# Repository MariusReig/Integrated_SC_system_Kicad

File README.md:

# Integrated_SC_system_Kicad
This repository contains the schematics and layout for an integrated supercapacitor system design.

Some changes is done in the schematic after the prototype was constructed. This includes:
- Removed schotky diode and auto-balancing in the cell balancing circuitry. 
- Adjusted cell-balancing resistance. 
- Adjusted pull-up resistor in the OVP. This is also done to the prototype.
- Charge and pre-charge gate-signal on isolated end is switched. 

Notes from testing of the prototype:
- The prototype is able to charge without any gatesignal through the pre-charge mosfet. Gatesignal is required to utilize charge and load. 
- The auto-balancing IC does not work as intended. Seems to be working for one cell of the two connected for each. Go back and check connections or use only resistor balancing. 
The design with balancing two-and-two cells is not great and needs work. Also caused the voltage potential over some odd-number cells to become negative. The voltage potential over the two first cells affected another, causing the even cell to receive more charge. A quick fix was to remove the IC and solder on 160ohm balancing resistance for each cell. The prototype was then balanced properly and tests was carried out. 
- The schotky diode was removed to test if it was a potential error-source. It was not. 
- The OVP circuit did not work. Since all 12 circuits are connected to the same 5V_ISO supply all will be pulled to ground unless all are active at the same time. The differential amplifier works as intended, but not the votlage detection IC. Tests on the IC can be carried out to check if it works as designed.

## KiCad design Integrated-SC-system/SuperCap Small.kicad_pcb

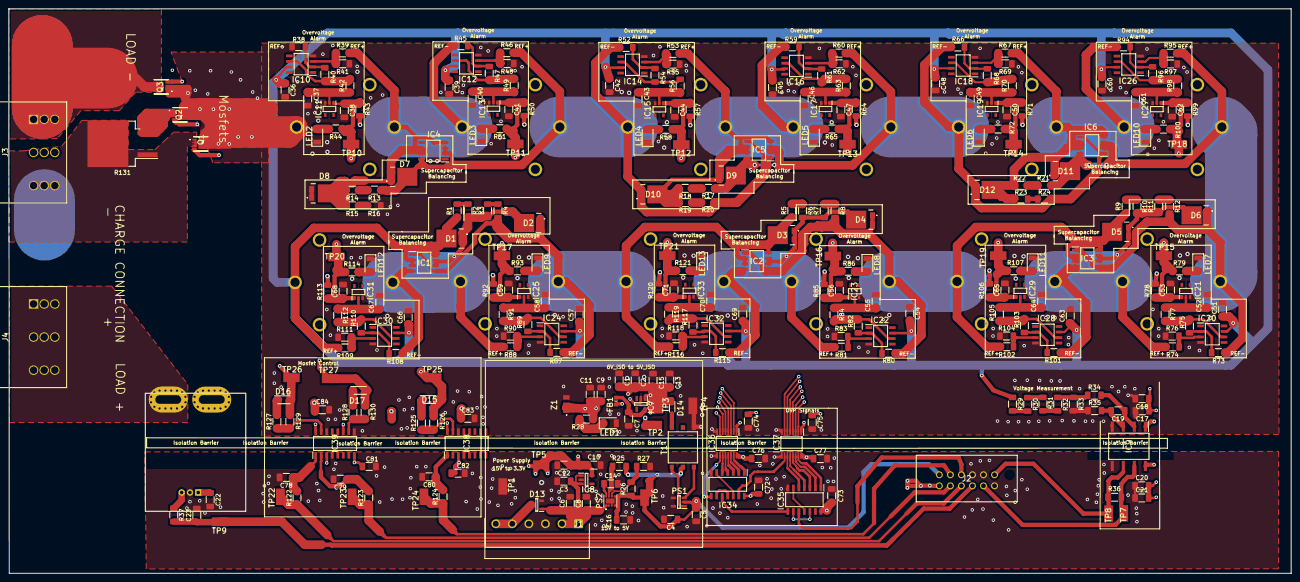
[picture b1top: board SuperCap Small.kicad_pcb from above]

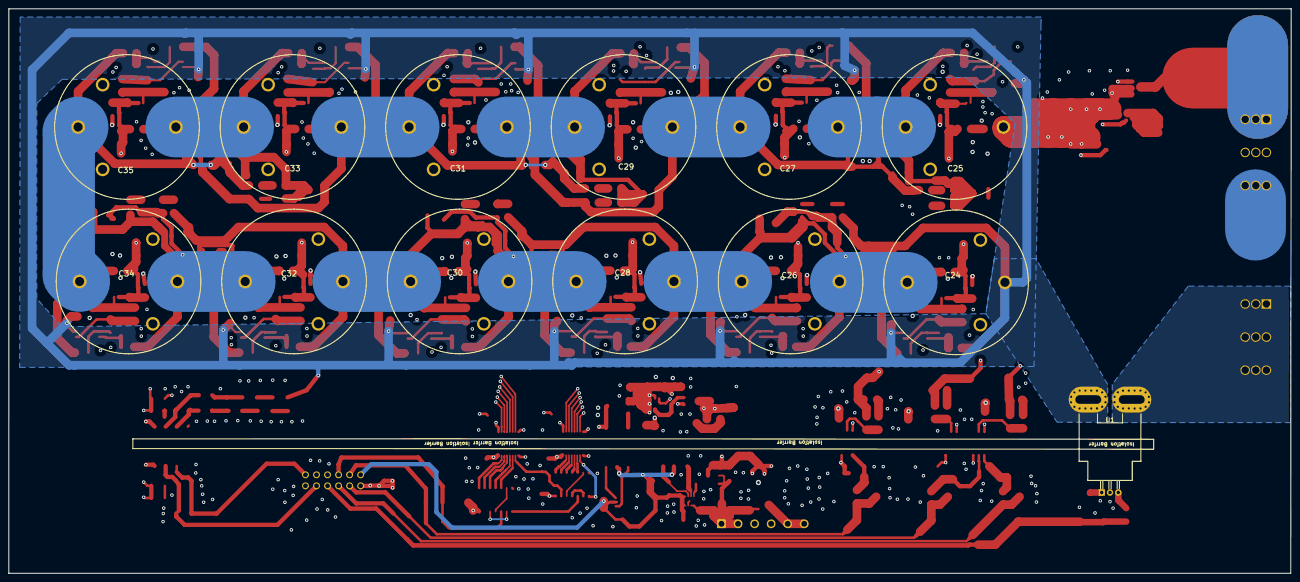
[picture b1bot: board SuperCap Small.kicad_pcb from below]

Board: 4 copper layers, 295.2 x 129.9 mm, 324 parts (13 on the bottom side), 159 nets.

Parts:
C1, C4, C7, C9, C13: 0.01u; C_1206_3216Metric_Pad1.33x1.80mm_HandSolder
C2, C5, C11, C12, C15: 100p; C_1206_3216Metric_Pad1.33x1.80mm_HandSolder
C3, C18, C21, C23, C83, C84: 1u; C_1206_3216Metric_Pad1.33x1.80mm_HandSolder
C6: 470p; C_1206_3216Metric_Pad1.33x1.80mm_HandSolder
C8: 10u; C_1206_3216Metric_Pad1.33x1.80mm_HandSolder
C10: 2.2u; C_1206_3216Metric_Pad1.33x1.80mm_HandSolder
C14: 430p; C_1206_3216Metric_Pad1.33x1.80mm_HandSolder
C16: 22u; C_1206_3216Metric_Pad1.33x1.80mm_HandSolder
C17, C20, C22, C36, C37, C38, C39, C40, C41, C42, C43, C44, C45, C46, C47, C48, C49, C50, C51, C52, C53, C54, C55, C56, C57, C58, C59, C60, C61, C62, C63, C64, C65, C66, C67, C68, C69, C70, C71, C72, C73, C74, C75, C76, C77, C78, C79, C80, C81, C82: 0.1u; C_1206_3216Metric_Pad1.33x1.80mm_HandSolder
C19: 330p; C_1206_3216Metric_Pad1.33x1.80mm_HandSolder
C24, C25, C26, C27, C28, C29, C30, C31, C32, C33, C34, C35: BCAP0360_P270_S18; BCAP0350P270S18
D1, D2, D3, D4, D5, D6, D7, D8, D9, D10, D11, D12: FSV10100V; FSV20100V
D13: PESD15VL2BT,215; SOT95P230X110-3N
D14: PMEG2005EJ,115; SODFL2512X80N
D15, D16, D17: RS07D-HM3-08; SODFL3718X108N
FB1: MMZ1608B102CTA00; BEADC1608X95N
IC1, IC2, IC3, IC4, IC5, IC6: ALD910017SALI; SOIC127P600X175-8N
IC7: LD2985BM50R; SOT95P280X145-5N
IC8: MIC5225-3.3YM5-TR; SOT95P280X145-5N
IC9: AMC1100DUBR; SOP254P1040X485-8N
IC10, IC12, IC14, IC16, IC18, IC20, IC22, IC24, IC26, IC28, IC30, IC32: OPA197IDR; SOIC127P600X175-8N
IC11, IC13, IC15, IC17, IC19, IC21, IC23, IC25, IC27, IC29, IC31, IC33: BD4827G-TR; SOT95P280X125-5N
IC34, IC35: SN74HCS4075QDRQ1; SOIC127P600X175-14N
IC36, IC37: ISO7760FQDBQQ1; SOP64P600X175-16N
IC38, IC39: UCC21220AD; SOIC127P600X175-16N
J1: 691322310006; SHDRRA6W80P0X381_1X6_2405X920X700P
J2: 15-47-7512; 15477512
J3, J4: 1717017
LED1, LED2, LED3, LED4, LED5, LED6, LED7, LED8, LED9, LED10, LED11, LED12, LED13: APTD3216LSYCK; LEDC3216X200N
PS1: SN6501DBVR; SOT95P280X145-5N
PS2: TPS82130SILT
Q1, Q2, Q3: BSZ024N04LS6ATMA1
R1, R2, R3, R4, R5, R6, R7, R8, R9, R10, R11, R12, R13, R14, R15, R16, R17, R18, R19, R20, R21, R22, R23, R24, R44, R51, R58, R65, R72, R79, R86, R93, R100, R107, R114, R121: 400; R_1206_3216Metric_Pad1.30x1.75mm_HandSolder
R25, R27: 100k; R_1206_3216Metric_Pad1.30x1.75mm_HandSolder
R26: 523k; R_1206_3216Metric_Pad1.30x1.75mm_HandSolder
R28: 3.16; R_1206_3216Metric_Pad1.30x1.75mm_HandSolder
R29, R30, R31, R32: 59.7; R_1206_3216Metric_Pad1.30x1.75mm_HandSolder
R33, R43, R50, R57, R64, R71, R78, R85, R92, R99, R106, R113, R120: 1k; R_1206_3216Metric_Pad1.30x1.75mm_HandSolder
R34, R35: 12; R_1206_3216Metric_Pad1.30x1.75mm_HandSolder
R36, R37, R125, R126, R127, R128, R129, R130: R; R_1206_3216Metric_Pad1.30x1.75mm_HandSolder
R38, R39, R40, R41, R42, R45, R46, R47, R48, R49, R52, R53, R54, R55, R56, R59, R60, R61, R62, R63, R66, R67, R68, R69, R70, R73, R74, R75, R76, R77, R80, R81, R82, R83, R84, R87, R88, R89, R90, R91, R94, R95, R96, R97, R98, R101, R102, R103, R104, R105, R108, R109, R110, R111, R112, R115, R116, R117, R118, R119: 10k; R_1206_3216Metric_Pad1.30x1.75mm_HandSolder
R122, R123, R124: rc; R_1206_3216Metric_Pad1.30x1.75mm_HandSolder
R131: 30; TO-263-2_TabPin1
T1: 760390015
TP1, TP2, TP3, TP4, TP5, TP6, TP7, TP8, TP9, TP10, TP11, TP12, TP13, TP14, TP15, TP16, TP17, TP18, TP19, TP20, TP21, TP22, TP23, TP24, TP25, TP26, TP27: 5019
U1: ACS758LCB-050B-PFF-T; Allegro_CB_PFF
Z1: DFLZ6V2-7; DFLZ6V87

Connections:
3.3V: C10.1, C12.1, C20.2, C21.2, C22.1, C72.1, C73.1, C76.1, C77.1, C81.1, C82.1, IC8.5, IC9.8, IC34.14, IC35.14, IC36.16, IC37.16, IC38.3, IC39.3, IC39.8, J2.B6, TP5.1, U1.1
5V: C4.1, C5.1, C16.1, J2.A6, PS1.2, PS2.4, PS2.5, R25.1, R26.1, T1.2, TP6.1
5V_ISO: C9.2, C11.2, C17.1, C18.1, C74.1, C75.1, FB1.1, IC9.1, IC36.1, IC37.1, R28.1, R43.2, R50.2, R57.2, R64.2, R71.2, R78.2, R85.2, R92.2, R99.2, R106.2, R113.2, R120.2, TP2.1, Z1.1
6V_ISO: C1.2, C2.2, C13.2, C15.1, C83.1, C84.1, D14.1, IC7.1, IC38.16, IC39.11, IC39.16, TP3.1
15V_global: C3.1, C6.1, C8.1, D13.1, IC8.1, IC8.3, J1.1, J1.2, PS2.1, PS2.2
/Isolation-IC/IN_PORT_1: C68.1, IC31.1, IC36.7, R113.1, R114.1, TP20.1
/Isolation-IC/IN_PORT_2: C59.1, IC25.1, IC36.5, R92.1, R93.1, TP17.1
/Isolation-IC/IN_PORT_3: C71.1, IC33.1, IC36.2, R120.1, R121.1, TP21.1
/Isolation-IC/IN_PORT_4: C56.1, IC23.1, IC37.7, R85.1, R86.1, TP16.1
/Isolation-IC/IN_PORT_5: C65.1, IC29.1, IC37.4, R106.1, R107.1, TP19.1
/Isolation-IC/IN_PORT_6: C53.1, IC21.1, IC37.2, R78.1, R79.1, TP15.1
/Isolation-IC/IN_PORT_7: C62.1, IC27.1, IC37.3, R99.1, R100.1, TP18.1
/Isolation-IC/IN_PORT_8: C50.1, IC19.1, IC37.5, R71.1, R72.1, TP14.1
/Isolation-IC/IN_PORT_9: C47.1, IC17.1, IC37.6, R64.1, R65.1, TP13.1
/Isolation-IC/IN_PORT_10: C44.1, IC15.1, IC36.3, R57.1, R58.1, TP12.1
/Isolation-IC/IN_PORT_11: C41.1, IC13.1, IC36.4, R50.1, R51.1, TP11.1
/Isolation-IC/IN_PORT_12: C38.1, IC11.1, IC36.6, R43.1, R44.1, TP10.1
/OR-GATE/IN_PORT_1: IC34.8, IC36.10
/OR-GATE/IN_PORT_2: IC34.4, IC36.12
/OR-GATE/IN_PORT_3: IC34.1, IC36.15
/OR-GATE/IN_PORT_4: IC34.13, IC37.10
/OR-GATE/IN_PORT_5: IC35.3, IC37.13
/OR-GATE/IN_PORT_6: IC35.1, IC37.15
/OR-GATE/IN_PORT_7: IC35.4, IC37.12
/OR-GATE/IN_PORT_8: IC35.2, IC37.14
/OR-GATE/IN_PORT_9: IC35.5, IC37.11
/OR-GATE/IN_PORT_10: IC34.2, IC36.14
/OR-GATE/IN_PORT_11: IC34.3, IC36.13
/OR-GATE/IN_PORT_12: IC34.5, IC36.11
/Precharge/CHARGE_INN: J3.7, J3.8, J3.9, Q1.1, Q1.2, Q1.3, Q1.9, R131.1
/Precharge/Charge_Active: J2.B5, R123.1, TP23.1
/Precharge/LOAD_INN: J3.1, J3.2, J3.3, Q3.5, Q3.6, Q3.7, Q3.8, Q3.10
/Sheet6014032E/Current_TBM+: J4.1, J4.2, J4.3, J4.4, J4.5, J4.6, J4.7, J4.8, J4.9, U1.4
/Signaling/ADCINA0_AI: C23.1, J2.B3, R37.2, TP9.1
/Signaling/ADCINA2_AI: IC9.7, J2.B2, R36.1, TP7.1
/Signaling/ADCINA3_AI: IC9.6, J2.A1, R36.2, TP8.1
/Signaling/GPIO_P22: J2.A5, R124.1, TP24.1
/Signaling/GPIO_P52: IC35.10, J2.A4
/Signaling/GPIO_P97: J2.B4, R122.1, TP22.1
/Supercaps/OVP_V1-_V2+: C24.4, C26.1, D1.1, D1.2, D2.3, IC1.4, IC1.6, IC1.7, R2.2, R3.1, R88.2, R108.2
/Supercaps/OVP_V2-_V3+: C26.4, C28.1, D2.1, D2.2, D3.3, IC1.1, IC1.5, IC2.2, IC2.3, IC2.8, R4.2, R5.1, R87.2, R116.2
/Supercaps/OVP_V3-_V4+: C28.4, C30.1, D3.1, D3.2, D4.3, IC2.4, IC2.6, IC2.7, R6.2, R7.1, R81.2, R115.2
/Supercaps/OVP_V4-_V5+: C30.4, C32.1, D4.1, D4.2, D5.3, IC2.1, IC2.5, IC3.2, IC3.3, IC3.8, R8.2, R9.1, R80.2, R102.2
/Supercaps/OVP_V5-_V6+: C32.4, C34.1, D5.1, D5.2, D6.3, IC3.4, IC3.6, IC3.7, R10.2, R11.1, R74.2, R101.2
/Supercaps/OVP_V6-_V7+: C34.4, C35.1, D6.1, D6.2, D11.3, IC3.1, IC3.5, IC6.2, IC6.3, IC6.8, R12.2, R21.1, R73.2, R95.2
/Supercaps/OVP_V7-_V8+: C33.1, C35.4, D11.1, D11.2, D12.3, IC6.4, IC6.6, IC6.7, R22.2, R23.1, R67.2, R94.2
/Supercaps/OVP_V8-_V9+: C31.1, C33.4, D9.3, D12.1, D12.2, IC5.2, IC5.3, IC5.8, IC6.1, IC6.5, R17.1, R24.2, R60.2, R66.2
/Supercaps/OVP_V9-_V10+: C29.1, C31.4, D9.1, D9.2, D10.3, IC5.4, IC5.6, IC5.7, R18.2, R19.1, R53.2, R59.2
/Supercaps/OVP_V10-_V11+: C27.1, C29.4, D7.3, D10.1, D10.2, IC4.2, IC4.3, IC4.8, IC5.1, IC5.5, R13.1, R20.2, R46.2, R52.2
/Supercaps/OVP_V11-_V12+: C25.1, C27.4, D7.1, D7.2, D8.3, IC4.4, IC4.6, IC4.7, R14.2, R15.1, R39.2, R45.2
Charge_Gate: D16.2, Q1.4, R129.2, TP26.1
GND: C3.2, C4.2, C5.2, C6.2, C8.2, C10.2, C12.2, C14.2, C16.2, C20.1, C21.1, C22.2, C23.2, C72.2, C73.2, C76.2, C77.2, C78.2, C79.2, C80.2, C81.2, C82.2, D13.2, IC8.2, IC9.5, IC34.7, IC35.7, IC36.9, IC37.9, IC38.4, IC39.4, J1.3, J1.4, J2.A2, J2.A3, J2.B1, PS1.4, PS1.5, PS2.3, PS2.9, R27.2, TP1.1, U1.2
GNDD: C1.1, C2.1, C7.1, C9.1, C11.1, C13.1, C15.2, C17.2, C18.2, C25.4, C36.2, C37.2, C38.2, C39.2, C40.2, C41.2, C42.2, C43.2, C44.2, C45.2, C46.2, C47.2, C48.2, C49.2, C50.2, C51.2, C52.2, C53.2, C54.2, C55.2, C56.2, C57.2, C58.2, C59.2, C60.2, C61.2, C62.2, C63.2, C64.2, C65.2, C66.2, C67.2, C68.2, C69.2, C70.2, C71.2, C74.2, C75.2, C83.2, C84.2, D8.1, D8.2, IC4.1, IC4.5, IC7.2, IC9.4, IC10.4, IC11.3, IC12.4, IC13.3, IC14.4, IC15.3, IC16.4, IC17.3, IC18.4, IC19.3, IC20.4, IC21.3, IC22.4, IC23.3, IC24.4, IC25.3, IC26.4, IC27.3, IC28.4, IC29.3, IC30.4, IC31.3, IC32.4, IC33.3, IC36.8, IC37.8, IC38.14, IC39.9, IC39.14, LED1.2, LED2.1, LED3.1, LED4.1, LED5.1, LED6.1, LED7.1, LED8.1, LED9.1, LED10.1, LED11.1, LED12.1, LED13.1, Q1.5, Q1.6, Q1.7, Q1.8, Q1.10, Q2.5, Q2.6, Q2.7, Q2.8, Q2.10, Q3.1, Q3.2, Q3.3, Q3.9, R16.2, R33.2, R35.1, R38.2, R41.1, R48.1, R55.1, R62.1, R69.1, R76.1, R83.1, R90.1, R97.1, R104.1, R111.1, R118.1, T1.4, TP4.1, Z1.2
Load_Gate: D15.2, Q3.4, R126.2, TP25.1
unnamed: C7.2, FB1.2, IC7.5
unnamed: C14.1, PS2.8
unnamed: C19.1, IC9.2, R34.2
unnamed: C19.2, IC9.3, R35.2
unnamed: C37.1, IC11.2, R42.1
unnamed: C40.1, IC13.2, R49.1
unnamed: C43.1, IC15.2, R56.1
unnamed: C46.1, IC17.2, R63.1
unnamed: C49.1, IC19.2, R70.1
unnamed: C52.1, IC21.2, R77.1
unnamed: C55.1, IC23.2, R84.1
unnamed: C58.1, IC25.2, R91.1
unnamed: C61.1, IC27.2, R98.1
unnamed: C64.1, IC29.2, R105.1
unnamed: C67.1, IC31.2, R112.1
unnamed: C70.1, IC33.2, R119.1
unnamed: C78.1, IC39.1, R122.2
unnamed: C79.1, IC39.2, R123.2
unnamed: C80.1, IC38.1, R124.2
unnamed: D13.3, J1.5, J1.6
unnamed: D14.2, T1.6
unnamed: D15.1, R125.2
unnamed: D16.1, R127.2
unnamed: D17.1, R128.2
unnamed: IC10.2, R38.1, R40.2
unnamed: IC10.3, R39.1, R41.2
unnamed: IC10.6, R40.1, R42.2
unnamed: IC12.2, R45.1, R47.2
unnamed: IC12.3, R46.1, R48.2
unnamed: IC12.6, R47.1, R49.2
unnamed: IC14.2, R52.1, R54.2
unnamed: IC14.3, R53.1, R55.2
unnamed: IC14.6, R54.1, R56.2
unnamed: IC16.2, R59.1, R61.2
unnamed: IC16.3, R60.1, R62.2
unnamed: IC16.6, R61.1, R63.2
unnamed: IC18.2, R66.1, R68.2
unnamed: IC18.3, R67.1, R69.2
unnamed: IC18.6, R68.1, R70.2
unnamed: IC20.2, R73.1, R75.2
unnamed: IC20.3, R74.1, R76.2
unnamed: IC20.6, R75.1, R77.2
unnamed: IC22.2, R80.1, R82.2
unnamed: IC22.3, R81.1, R83.2
unnamed: IC22.6, R82.1, R84.2
unnamed: IC24.2, R87.1, R89.2
unnamed: IC24.3, R88.1, R90.2
unnamed: IC24.6, R89.1, R91.2
unnamed: IC26.2, R94.1, R96.2
unnamed: IC26.3, R95.1, R97.2
unnamed: IC26.6, R96.1, R98.2
unnamed: IC28.2, R101.1, R103.2
unnamed: IC28.3, R102.1, R104.2
unnamed: IC28.6, R103.1, R105.2
unnamed: IC30.2, R108.1, R110.2
unnamed: IC30.3, R109.1, R111.2
unnamed: IC30.6, R110.1, R112.2
unnamed: IC32.2, R115.1, R117.2
unnamed: IC32.3, R116.1, R118.2
unnamed: IC32.6, R117.1, R119.2
unnamed: IC34.10, IC35.8
unnamed: IC34.9, IC34.11
unnamed: IC34.6, IC34.12
unnamed: IC35.6, IC35.11
unnamed: IC35.9, IC35.12
unnamed: IC38.15, R125.1, R126.1
unnamed: IC39.10, R128.1, R130.1
unnamed: IC39.15, R127.1, R129.1
unnamed: LED1.1, R28.2
unnamed: LED2.2, R44.2
unnamed: LED3.2, R51.2
unnamed: LED4.2, R58.2
unnamed: LED5.2, R65.2
unnamed: LED6.2, R72.2
unnamed: LED7.2, R79.2
unnamed: LED8.2, R86.2
unnamed: LED9.2, R93.2
unnamed: LED10.2, R100.2
unnamed: LED11.2, R107.2
unnamed: LED12.2, R114.2
unnamed: LED13.2, R121.2
unnamed: PS1.1, T1.1
unnamed: PS1.3, T1.3
unnamed: PS2.6, R26.2, R27.1
unnamed: PS2.7, R25.2
unnamed: Q2.1, Q2.2, Q2.3, Q2.9, R131.2
unnamed: R1.2, R2.1
unnamed: R3.2, R4.1
unnamed: R5.2, R6.1
unnamed: R7.2, R8.1
unnamed: R9.2, R10.1
unnamed: R11.2, R12.1
unnamed: R13.2, R14.1
unnamed: R15.2, R16.1
unnamed: R17.2, R18.1
unnamed: R19.2, R20.1
unnamed: R21.2, R22.1
unnamed: R23.2, R24.1
unnamed: R29.2, R30.1
unnamed: R30.2, R31.1
unnamed: R31.2, R32.1
unnamed: R32.2, R33.1, R34.1
unnamed: R37.1, U1.3
OVP_POWER: C24.1, C36.1, C39.1, C42.1, C45.1, C48.1, C51.1, C54.1, C57.1, C60.1, C63.1, C66.1, C69.1, D1.3, IC1.2, IC1.3, IC1.8, IC10.7, IC12.7, IC14.7, IC16.7, IC18.7, IC20.7, IC22.7, IC24.7, IC26.7, IC28.7, IC30.7, IC32.7, R1.1, R29.1, R109.2, U1.5
Precharge_Gate: D17.2, Q2.4, R130.2, TP27.1

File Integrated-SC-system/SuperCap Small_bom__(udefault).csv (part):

Component,Description,Part,References,Value,Footprint,Quantity Per PCB,Datasheet,Mouser Part Number,Mouser Price/Stock,Manufacturer_Name,Height,Manufacturer_Part_Number,Arrow Part Number,Arrow Price/Stock
1,Unpolarized capacitor,C,C2 C5 C11 C12 C15,100p,C_1206_3216Metric_Pad1.33x1.80mm_HandSolder,5,~,581-12063A101FAT2A,https://no.mouser.com/ProductDetail/AVX/12063A101FAT2A?qs=Y1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,,,,,
2,Unpolarized capacitor,C,C19,330p,C_1206_3216Metric_Pad1.33x1.80mm_HandSolder,1,~,80-C1206C331F3HACTU,https://no.mouser.com/ProductDetail/KEMET/C1206C331F3HACTU?q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,,,,,
3,Unpolarized capacitor,C,C14,430p,C_1206_3216Metric_Pad1.33x1.80mm_HandSolder,1,~,77-VJ12A100V431J,https://no.mouser.com/ProductDetail/Vishay-Vitramon/VJ1206A4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,,,,,
4,Unpolarized capacitor,C,C6,470p,C_1206_3216Metric_Pad1.33x1.80mm_HandSolder,1,~,80-C1206C471F5G,https://no.mouser.com/ProductDetail/KEMET/C1206C471F5GACTU?q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,,,,,
5,Unpolarized capacitor,C,C1 C4 C7 C9 C13,0.01u,C_1206_3216Metric_Pad1.33x1.80mm_HandSolder,5,~,80-C1206C103F3GECAUT,https://no.mouser.com/ProductDetail/KEMET/C1206C103F3GECAUTO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,,,,,
6,Unpolarized capacitor,C,C17 C20 C22 C36 C37 C38 C39 C40 C41 C42 C43 C44 C45 C46 C47 C48 C49 C50 C51 C52 C53 C54 C55 C56 C57 C58 C59 C60 C61 C62 C63 C64 C65 C66 C67 C68 C69 C70 C71 C72 C73 C74 C75 C76 C77 C78 C79 C80 C81 C82,0.1u,C_1206_3216Metric_Pad1.33x1.80mm_HandSolder,50,~,80-C1206C104F5JACTU,https://no.mouser.com/ProductDetail/KEMET/C1206C104F5JAC7800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,,,,,
7,Unpolarized capacitor,C,C3 C18 C21 C23 C83 C84,1u,C_1206_3216Metric_Pad1.33x1.80mm_HandSolder,6,~,80-C1206C105J3R,https://no.mouser.com/ProductDetail/KEMET/C1206C105J3RACTU?q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,,,,,
8,Unpolarized capacitor,C,C10,2.2u,C_1206_3216Metric_Pad1.33x1.80mm_HandSolder,1,~,80-C1206C225J4RECLR,https://no.mouser.com/ProductDetail/KEMET/C1206C225J4REC7210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,,,,,
9,Unpolarized capacitor,C,C8,10u,C_1206_3216Metric_Pad1.33x1.80mm_HandSolder,1,~,80-C1206C106J3RAUTO,https://no.mouser.com/ProductDetail/KEMET/C1206C106J3RACAUTO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,,,,,
10,Unpolarized capacitor,C,C16,22u,C_1206_3216Metric_Pad1.33x1.80mm_HandSolder,1,~,80-C1206C226K8R7210,https://no.mouser.com/ProductDetail/KEMET/C1206C226K8RAC7210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,,,,,
11,"Supercapacitors / Ultracapacitors 2.7V, 360F, snap-in",BCAP0360_P270_S18,C24 C25 C26 C27 C28 C29 C30 C31 C32 C33 C34 C35,BCAP0360_P270_S18,BCAP0350P270S18,12,https://componentsearchengine.com/Datasheets/1/BCAP0350 P270 S18.pdf,723-BCAP0360P270S18,https://www.mouser.co.uk/ProductDetail/Maxwell-Nesscap/BCAP0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,Maxwell / Nesscap,63,BCAP0360 P270 S18,,
12,"ON SEMICONDUCTOR - FSV10100V - SCHOTTKY RECT, AEC-Q101, 100V, TO-277",FSV10100V,D1 D2 D3 D4 D5 D6 D7 D8 D9 D10 D11 D12,FSV10100V,FSV20100V,12,https://www.onsemi.com/pub/Collateral/FSV10100V-D.PDF,512-FSV10100V,https://www.mouser.co.uk/ProductDetail/ON-Semiconductor-Fair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,ON Semiconductor,1.2,FSV10100V,FSV10100V,https://www.arrow.com/en/products/fsv10100v/on-semiconductor
13,,"PESD15VL2BT,215",D13,"PESD15VL2BT,215",SOT95P230X110-3N,1,http://uk.rs-online.com/web/p/products/1242372,771-PESD15VL2BT-T/R,https://www.mouser.co.uk/ProductDetail/Nexperia/PESD15VL2BT2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,Nexperia,1.1,"PESD15VL2BT,215","PESD15VL2BT,215",https://www.arrow.com/en/products/pesd15vl2bt215/nexperia
14,"NEXPERIA - PMEG2005EJ,115 - Schottky Rectifier, 20 V, 500 mA, Single, SOD-323F, 2 Pins, 390 mV","PMEG2005EJ,115",D14,"PMEG2005EJ,115",SODFL2512X80N,1,"https://ms.componentsearchengine.com/Datasheets/2/PMEG2005EJ,115.pdf",771-PMEG2005EJ115,https://www.mouser.co.uk/ProductDetail/Nexperia/PMEG2005EJ11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,Nexperia,0.8,"PMEG2005EJ,115","PMEG2005EJ,115",https://www.arrow.com/en/products/pmeg2005ej115/nexperia
15,Rectifiers 1.4A 200V,RS07D-HM3-08,D15 D16 D17,RS07D-HM3-08,SODFL3718X108N,3,https://www.vishay.com/docs/85195/rs07bm.pdf,78-RS07D-HM3-08,https://www.mouser.co.uk/ProductDetail/Vishay-Semiconductors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,Vishay,1.08,RS07D-HM3-08,,
16,Ferrite Beads 1K OHM 25%,MMZ1608B102CTA00,FB1,MMZ1608B102CTA00,BEADC1608X95N,1,https://product.tdk.com/info/en/catalog/datasheets/beads_com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,810-MMZ1608B102CTA00,https://www.mouser.co.uk/ProductDetail/TDK/MMZ1608B102CTA00/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,TDK,0.95,MMZ1608B102CTA00,MMZ1608B102CTA00,https://www.arrow.com/en/products/mmz1608b102cta00/tdk
17,MOSFET Dual SAB MOSFET ARRAY VT=2.10V,ALD910021SALI,IC1 IC2 IC3 IC4 IC5 IC6,ALD910017SALI,SOIC127P600X175-8N,6,https://no.mouser.com/datasheet/2/8/ALD810017-464290.pdf,585-ALD910017SALI,https://no.mouser.com/ProductDetail/Advanced-Linear-Devices/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,Advanced Linear Devices Inc.,1.75,ALD910017SALI,,
18,"+/-250 mV-Input, Low-Cost Basic Isolated Amplifier for Current Sensing",AMC1100DUBR,IC9,AMC1100DUBR,SOP254P1040X485-8N,1,http://www.ti.com/lit/gpn/amc1100,595-AMC1100DUBR,https://www.mouser.co.uk/ProductDetail/Texas-Instruments/AMC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,Texas Instruments,4.85,AMC1100DUBR,AMC1100DUBR,https://www.arrow.com/en/products/amc1100dubr/texas-instruments
19,"Standard Voltage Detectors: ROHM CMOS reset ICs provide low current consumption and high accuracy. The extensive lineup includes both Nch Open Drain and CMOS output types in a wide range of detection voltages (from 2.3V to 6.0V, in 0.1V steps), enabling selection of the ideal solution based on customer requirements. In addition, the entire series is of course both lead-free and RoHS-compliant.",BD4827G-TR,IC11 IC13 IC15 IC17 IC19 IC21 IC23 IC25 IC27 IC29 IC31 IC33,BD4827G-TR,SOT95P280X125-5N,12,https://www.rohm.com/datasheet/BD4827G/bd48xxg-e,755-BD4827G-TR,https://www.mouser.co.uk/ProductDetail/ROHM-Semiconductor/BD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,ROHM Semiconductor,1.25,BD4827G-TR,,
20,"Automotive, high speed, robust EMC six-channel digital isolator",ISO7760FQDBQQ1,IC36 IC37,ISO7760FQDBQQ1,SOP64P600X175-16N,2,http://www.ti.com/lit/gpn/ISO7760-Q1,595-ISO7760FQDBQQ1,https://www.mouser.co.uk/ProductDetail/Texas-Instruments/ISO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,Texas Instruments,1.75,ISO7760FQDBQQ1,ISO7760FQDBQQ1,https://www.arrow.com/en/products/iso7760fqdbqq1/texas-instruments
21,"LDO Regulator 5V 0.15A SOT23-5 LD2985BM50R, Low Dropout Voltage Regulator, 0.15A, 5 V, 2.5  16 Vin, 5-Pin SOT-23",LD2985BM50R,IC7,LD2985BM50R,SOT95P280X145-5N,1,http://www.st.com/st-web-ui/static/active/en/resource/techni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,511-LD2985BM50,https://www.mouser.co.uk/ProductDetail/STMicroelectronics/LD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,STMicroelectronics,1.45,LD2985BM50R,LD2985BM50R,https://www.arrow.com/en/products/ld2985bm50r/stmicroelectronics
22,"MICROCHIP - MIC5225-3.3YM5-TR - LDO, REG, 16VIN, 0.15A, 3.3V, 2%, 5SOT23",MIC5225-3.3YM5-TR,IC8,MIC5225-3.3YM5-TR,SOT95P280X145-5N,1,http://www.farnell.com/datasheets/1580469.pdf,998-MIC5225-3.3YM5TR,https://www.mouser.co.uk/ProductDetail/Microchip-Technology-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,Microchip,1.45,MIC5225-3.3YM5-TR,MIC5225-3.3YM5-TR,https://www.arrow.com/en/products/mic5225-3.3ym5-tr/microchi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
23,"36-V, Precision, Rail-to-Rail Input Output, Low Offset Voltage Op Amp",OPA197IDR,IC10 IC12 IC14 IC16 IC18 IC20 IC22 IC24 IC26 IC28 IC30 IC32,OPA197IDR,SOIC127P600X175-8N,12,http://www.ti.com/lit/gpn/opa197,595-OPA197IDR,https://www.mouser.co.uk/ProductDetail/Texas-Instruments/OPA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,Texas Instruments,1.75,OPA197IDR,OPA197IDR,https://www.arrow.com/en/products/opa197idr/texas-instruments
24,Logic Gates Automotive triple 3-input OR gates with Schmitt-trigger inputs 14-SOIC -40 to 125,SN74HCS4075QDRQ1,IC34 IC35,SN74HCS4075QDRQ1,SOIC127P600X175-14N,2,http://www.ti.com/lit/ds/symlink/sn74hcs4075-q1.pdf,595-SN74HCS4075QDRQ1,https://www.mouser.co.uk/ProductDetail/Texas-Instruments/SN7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,Texas Instruments,1.75,SN74HCS4075QDRQ1,,
25,"4-A, 6-A, 3.0-kVRMS Isolated Dual-Channel Gate Driver",UCC21220AD,IC38 IC39,UCC21220AD,SOIC127P600X175-16N,2,http://www.ti.com/lit/gpn/UCC21220A,595-UCC21220AD,https://www.mouser.co.uk/ProductDetail/Texas-Instruments/UCC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,Texas Instruments,1.75,UCC21220AD,UCC21220AD,https://www.arrow.com/en/products/ucc21220ad/texas-instruments
26,Headers & Wire Housings CGrid VT Shrd Hdr w/Pg TIN 12Ckt,15-47-7512,J2,15-47-7512,15477512,1,https://componentsearchengine.com/Datasheets/1/15-47-7512.pdf,538-15-47-7512,https://www.mouser.co.uk/ProductDetail/Molex/15-47-7512?qs=R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,Molex,11.18,15-47-7512,,
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
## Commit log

2021-05-30 Official release
